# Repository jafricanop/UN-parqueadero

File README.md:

# UN-parqueadero
#Proyecto de Taller de Ingenieria Electronica

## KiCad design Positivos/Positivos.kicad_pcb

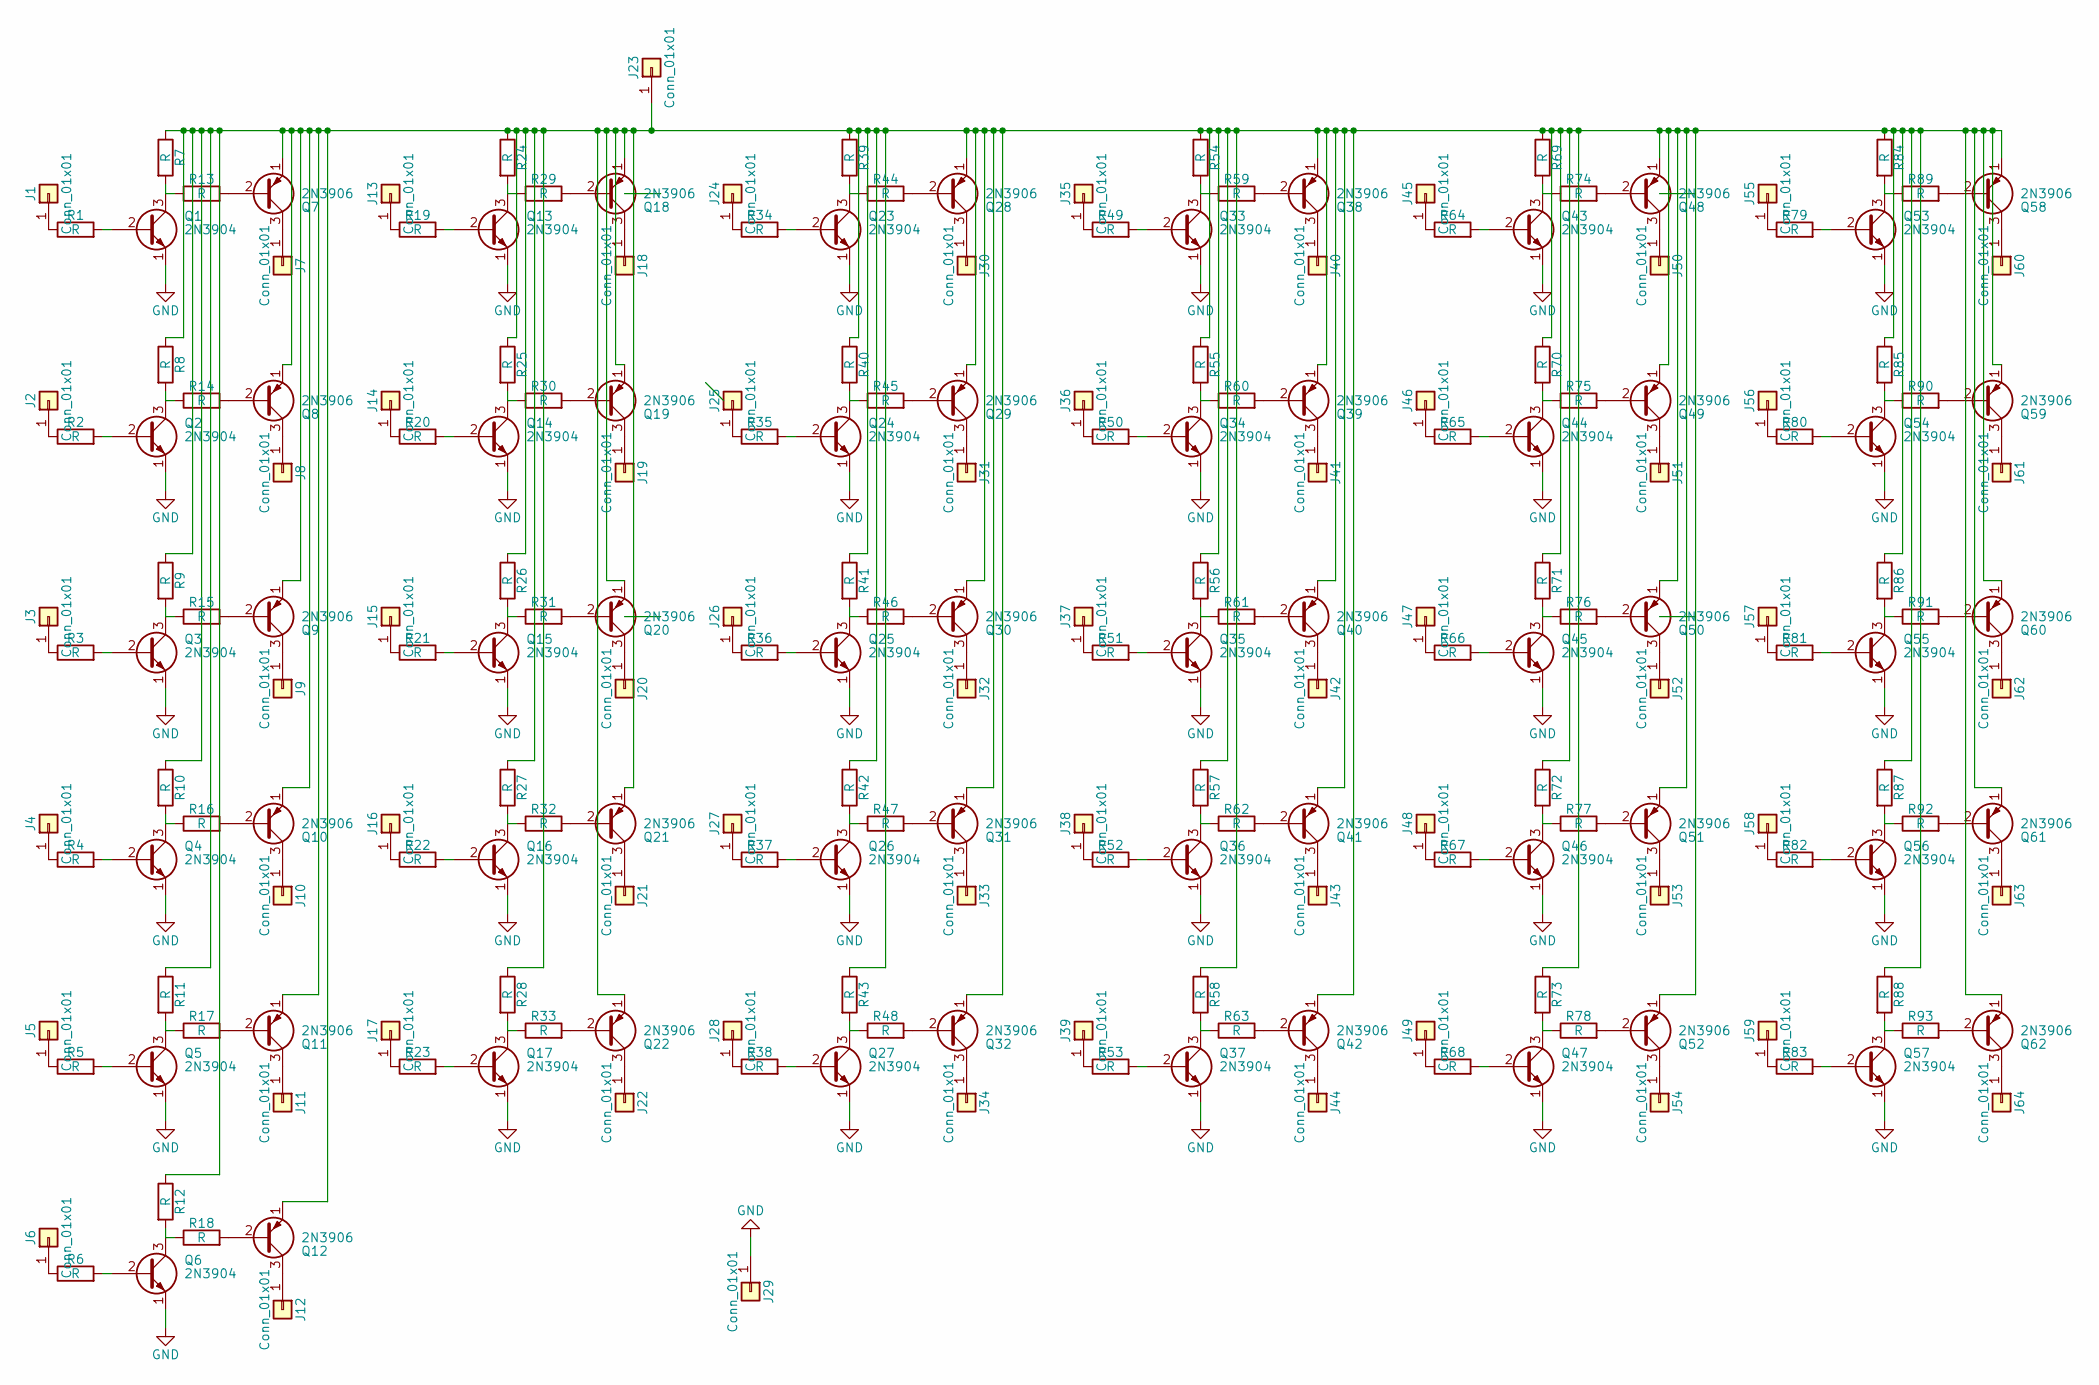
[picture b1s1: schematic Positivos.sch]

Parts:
J1, J2, J3, J4, J5, J6, J7, J8, J9, J10, J11, J12, J13, J14, J15, J16, J17, J18, J19, J20, J21, J22, J23, J24, J25, J26, J27, J28, J29, J30, J31, J32, J33, J34, J35, J36, J37, J38, J39, J40, J41, J42, J43, J44, J45, J46, J47, J48, J49, J50, J51, J52, J53, J54, J55, J56, J57, J58, J59, J60, J61, J62, J63, J64: Conn_01x01; 1pin
Q1, Q2, Q3, Q4, Q5, Q6, Q13, Q14, Q15, Q16, Q17, Q23, Q24, Q25, Q26, Q27, Q33, Q34, Q35, Q36, Q37, Q43, Q44, Q45, Q46, Q47, Q53, Q54, Q55, Q56, Q57: 2N3904; OldSowjetaera_Transistor_Type-I_SmallPads
Q7, Q8, Q9, Q10, Q11, Q12, Q18, Q19, Q20, Q21, Q22, Q28, Q29, Q30, Q31, Q32, Q38, Q39, Q40, Q41, Q42, Q48, Q49, Q50, Q51, Q52, Q58, Q59, Q60, Q61, Q62: 2N3906; OldSowjetaera_Transistor_Type-I_SmallPads
R1, R2, R3, R4, R5, R6, R7, R8, R9, R10, R11, R12, R13, R14, R15, R16, R17, R18, R19, R20, R21, R22, R23, R24, R25, R26, R27, R28, R29, R30, R31, R32, R33, R34, R35, R36, R37, R38, R39, R40, R41, R42, R43, R44, R45, R46, R47, R48, R49, R50, R51, R52, R53, R54, R55, R56, R57, R58, R59, R60, R61, R62, R63, R64, R65, R66, R67, R68, R69, R70, R71, R72, R73, R74, R75, R76, R77, R78, R79, R80, R81, R82, R83, R84, R85, R86, R87, R88, R89, R90, R91, R92, R93: R; R_Axial_DIN0207_L6.3mm_D2.5mm_P10.16mm_Horizontal

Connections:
GND: J29.1, Q1.1 (E), Q2.1 (E), Q3.1 (E), Q4.1 (E), Q5.1 (E), Q6.1 (E), Q13.1 (E), Q14.1 (E), Q15.1 (E), Q16.1 (E), Q17.1 (E), Q23.1 (E), Q24.1 (E), Q25.1 (E), Q26.1 (E), Q27.1 (E), Q33.1 (E), Q34.1 (E), Q35.1 (E), Q36.1 (E), Q37.1 (E), Q43.1 (E), Q44.1 (E), Q45.1 (E), Q46.1 (E), Q47.1 (E), Q53.1 (E), Q54.1 (E), Q55.1 (E), Q56.1 (E), Q57.1 (E)
unnamed: J1.1, R1.1
unnamed: J2.1, R2.1
unnamed: J3.1, R3.1
unnamed: J4.1, R4.1
unnamed: J5.1, R5.1
unnamed: J6.1, R6.1
unnamed: J7.1, Q7.3 (C)
unnamed: J8.1, Q8.3 (C)
unnamed: J9.1, Q9.3 (C)
unnamed: J10.1, Q10.3 (C)
unnamed: J11.1, Q11.3 (C)
unnamed: J12.1, Q12.3 (C)
unnamed: J13.1, R19.1
unnamed: J14.1, R20.1
unnamed: J15.1, R21.1
unnamed: J16.1, R22.1
unnamed: J17.1, R23.1
unnamed: J18.1, Q18.3 (C)
unnamed: J19.1, Q19.3 (C)
unnamed: J20.1, Q20.3 (C)
unnamed: J21.1, Q21.3 (C)
unnamed: J22.1, Q22.3 (C)
unnamed: J23.1, Q7.1 (E), Q8.1 (E), Q9.1 (E), Q10.1 (E), Q11.1 (E), Q12.1 (E), Q18.1 (E), Q19.1 (E), Q20.1 (E), Q21.1 (E), Q22.1 (E), Q28.1 (E), Q29.1 (E), Q30.1 (E), Q31.1 (E), Q32.1 (E), Q38.1 (E), Q39.1 (E), Q40.1 (E), Q41.1 (E), Q42.1 (E), Q48.1 (E), Q49.1 (E), Q50.1 (E), Q51.1 (E), Q52.1 (E), Q58.1 (E), Q59.1 (E), Q60.1 (E), Q61.1 (E), Q62.1 (E), R7.1, R8.1, R9.1, R10.1, R11.1, R12.1, R24.1, R25.1, R26.1, R27.1, R28.1, R39.1, R40.1, R41.1, R42.1, R43.1, R54.1, R55.1, R56.1, R57.1, R58.1, R69.1, R70.1, R71.1, R72.1, R73.1, R84.1, R85.1, R86.1, R87.1, R88.1
unnamed: J24.1, R34.1
unnamed: J25.1, R35.1
unnamed: J26.1, R36.1
unnamed: J27.1, R37.1
unnamed: J28.1, R38.1
unnamed: J30.1, Q28.3 (C)
unnamed: J31.1, Q29.3 (C)
unnamed: J32.1, Q30.3 (C)
unnamed: J33.1, Q31.3 (C)
unnamed: J34.1, Q32.3 (C)
unnamed: J35.1, R49.1
unnamed: J36.1, R50.1
unnamed: J37.1, R51.1
unnamed: J38.1, R52.1
unnamed: J39.1, R53.1
unnamed: J40.1, Q38.3 (C)
unnamed: J41.1, Q39.3 (C)
unnamed: J42.1, Q40.3 (C)
unnamed: J43.1, Q41.3 (C)
unnamed: J44.1, Q42.3 (C)
unnamed: J45.1, R64.1
unnamed: J46.1, R65.1
unnamed: J47.1, R66.1
unnamed: J48.1, R67.1
unnamed: J49.1, R68.1
unnamed: J50.1, Q48.3 (C)
unnamed: J51.1, Q49.3 (C)
unnamed: J52.1, Q50.3 (C)
unnamed: J53.1, Q51.3 (C)
unnamed: J54.1, Q52.3 (C)
unnamed: J55.1, R79.1
unnamed: J56.1, R80.1
unnamed: J57.1, R81.1
unnamed: J58.1, R82.1
unnamed: J59.1, R83.1
unnamed: J60.1, Q58.3 (C)
unnamed: J61.1, Q59.3 (C)
unnamed: J62.1, Q60.3 (C)
unnamed: J63.1, Q61.3 (C)
unnamed: J64.1, Q62.3 (C)
unnamed: Q1.2 (B), R1.2
unnamed: Q1.3 (C), R7.2, R13.1
unnamed: Q2.2 (B), R2.2
unnamed: Q2.3 (C), R8.2, R14.1
unnamed: Q3.2 (B), R3.2
unnamed: Q3.3 (C), R9.2, R15.1
unnamed: Q4.2 (B), R4.2
unnamed: Q4.3 (C), R10.2, R16.1
unnamed: Q5.2 (B), R5.2
unnamed: Q5.3 (C), R11.2, R17.1
unnamed: Q6.2 (B), R6.2
unnamed: Q6.3 (C), R12.2, R18.1
unnamed: Q7.2 (B), R13.2
unnamed: Q8.2 (B), R14.2
unnamed: Q9.2 (B), R15.2
unnamed: Q10.2 (B), R16.2
unnamed: Q11.2 (B), R17.2
unnamed: Q12.2 (B), R18.2
unnamed: Q13.2 (B), R19.2
unnamed: Q13.3 (C), R24.2, R29.1
unnamed: Q14.2 (B), R20.2
unnamed: Q14.3 (C), R25.2, R30.1
unnamed: Q15.2 (B), R21.2
unnamed: Q15.3 (C), R26.2, R31.1
unnamed: Q16.2 (B), R22.2
unnamed: Q16.3 (C), R27.2, R32.1
unnamed: Q17.2 (B), R23.2
unnamed: Q17.3 (C), R28.2, R33.1
unnamed: Q18.2 (B), R29.2
unnamed: Q19.2 (B), R30.2
unnamed: Q20.2 (B), R31.2
unnamed: Q21.2 (B), R32.2
unnamed: Q22.2 (B), R33.2
unnamed: Q23.2 (B), R34.2
unnamed: Q23.3 (C), R39.2, R44.1
unnamed: Q24.2 (B), R35.2
unnamed: Q24.3 (C), R40.2, R45.1
unnamed: Q25.2 (B), R36.2
unnamed: Q25.3 (C), R41.2, R46.1
unnamed: Q26.2 (B), R37.2
unnamed: Q26.3 (C), R42.2, R47.1
unnamed: Q27.2 (B), R38.2
unnamed: Q27.3 (C), R43.2, R48.1
unnamed: Q28.2 (B), R44.2
unnamed: Q29.2 (B), R45.2
unnamed: Q30.2 (B), R46.2
unnamed: Q31.2 (B), R47.2
unnamed: Q32.2 (B), R48.2
unnamed: Q33.2 (B), R49.2
unnamed: Q33.3 (C), R54.2, R59.1
unnamed: Q34.2 (B), R50.2
unnamed: Q34.3 (C), R55.2, R60.1
unnamed: Q35.2 (B), R51.2
unnamed: Q35.3 (C), R56.2, R61.1
unnamed: Q36.2 (B), R52.2
unnamed: Q36.3 (C), R57.2, R62.1
unnamed: Q37.2 (B), R53.2
unnamed: Q37.3 (C), R58.2, R63.1
unnamed: Q38.2 (B), R59.2
unnamed: Q39.2 (B), R60.2
unnamed: Q40.2 (B), R61.2
unnamed: Q41.2 (B), R62.2
unnamed: Q42.2 (B), R63.2
unnamed: Q43.2 (B), R64.2
unnamed: Q43.3 (C), R69.2, R74.1
unnamed: Q44.2 (B), R65.2
unnamed: Q44.3 (C), R70.2, R75.1
unnamed: Q45.2 (B), R66.2
unnamed: Q45.3 (C), R71.2, R76.1
unnamed: Q46.2 (B), R67.2
unnamed: Q46.3 (C), R72.2, R77.1
unnamed: Q47.2 (B), R68.2
unnamed: Q47.3 (C), R73.2, R78.1
unnamed: Q48.2 (B), R74.2
unnamed: Q49.2 (B), R75.2
unnamed: Q50.2 (B), R76.2
unnamed: Q51.2 (B), R77.2
unnamed: Q52.2 (B), R78.2
unnamed: Q53.2 (B), R79.2
unnamed: Q53.3 (C), R84.2, R89.1
unnamed: Q54.2 (B), R80.2
unnamed: Q54.3 (C), R85.2, R90.1
unnamed: Q55.2 (B), R81.2
unnamed: Q55.3 (C), R86.2, R91.1
unnamed: Q56.2 (B), R82.2
unnamed: Q56.3 (C), R87.2, R92.1
unnamed: Q57.2 (B), R83.2
unnamed: Q57.3 (C), R88.2, R93.1
unnamed: Q58.2 (B), R89.2
unnamed: Q59.2 (B), R90.2
unnamed: Q60.2 (B), R91.2
unnamed: Q61.2 (B), R92.2
unnamed: Q62.2 (B), R93.2

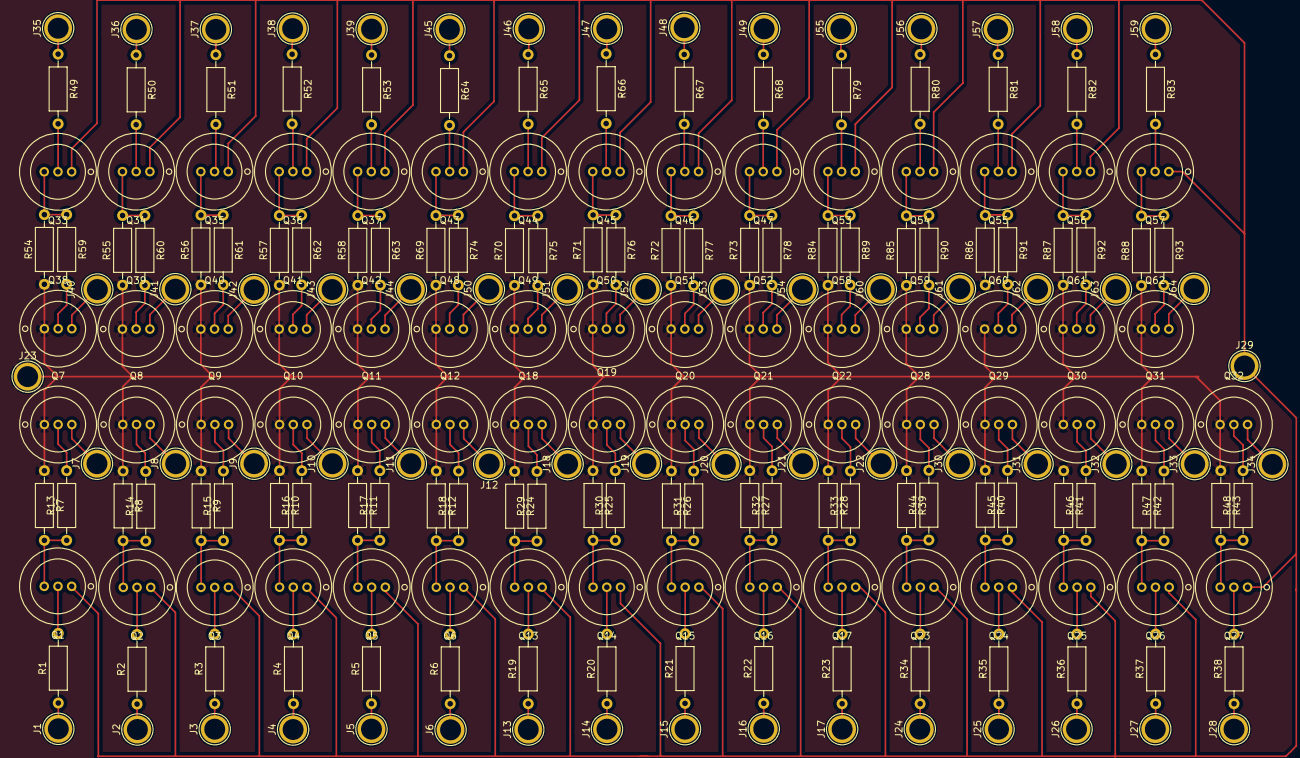
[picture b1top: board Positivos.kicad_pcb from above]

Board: 2 copper layers, 219 parts (0 on the bottom side), 157 nets.

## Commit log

2017-11-12 Esquema circuito
2017-11-12 Librerias Proteus
2017-11-13 Circuito Impreso
2017-11-16 Create Divisor de Voltaje
